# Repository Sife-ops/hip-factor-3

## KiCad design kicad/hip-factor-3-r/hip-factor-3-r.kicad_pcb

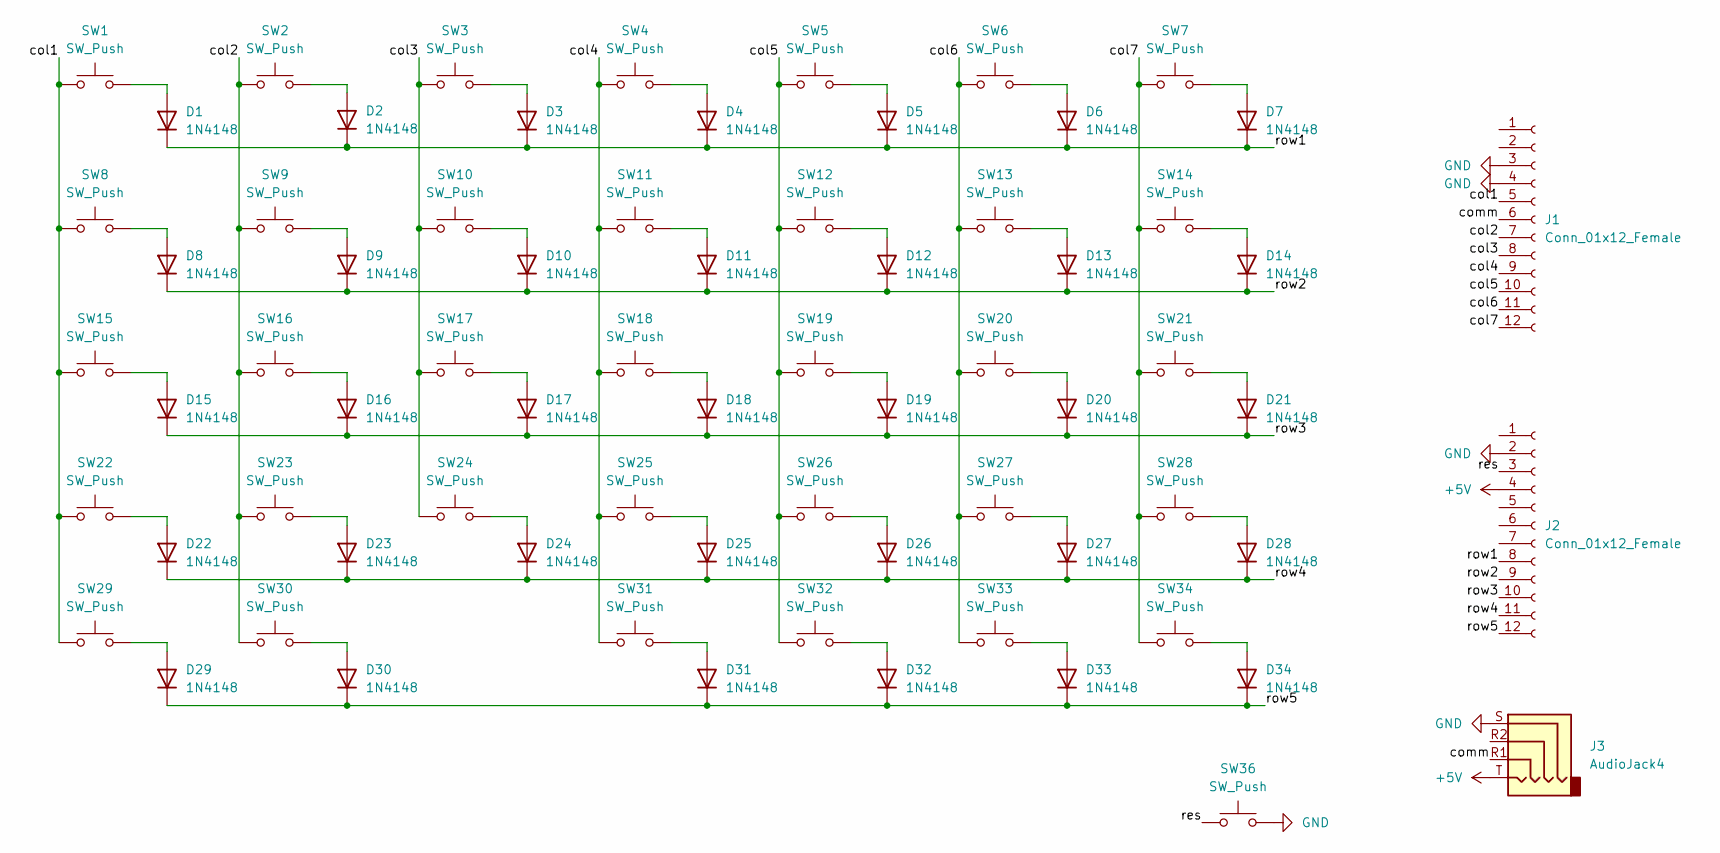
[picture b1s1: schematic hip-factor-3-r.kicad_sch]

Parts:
D1, D2, D3, D4, D5, D6, D7, D8, D9, D10, D11, D12, D13, D14, D15, D16, D17, D18, D19, D20, D21, D22, D23, D24, D25, D26, D27, D28, D29, D30, D31, D32, D33, D34: 1N4148
J1, J2: Conn_01x12_Female; PinHeader_1x12_P2.54mm_Vertical
J3: AudioJack4
SW1, SW2, SW3, SW4, SW5, SW6, SW7, SW8, SW9, SW10, SW11, SW12, SW13, SW14, SW15, SW16, SW17, SW18, SW19, SW20, SW21, SW22, SW23, SW24, SW25, SW26, SW27, SW28, SW29, SW30, SW31, SW32, SW33, SW34: SW_Push; SW_Cherry_MX_1.00u_Plate
SW36: SW_Push

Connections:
+5V: J2.4, J3.T
/col1: J1.5, SW1.1, SW8.1, SW15.1, SW22.1, SW29.1
/col2: J1.7, SW2.1, SW9.1, SW16.1, SW23.1, SW30.1
/col3: J1.8, SW3.1, SW10.1, SW17.1, SW24.1
/col4: J1.9, SW4.1, SW11.1, SW18.1, SW25.1, SW31.1
/col5: J1.10, SW5.1, SW12.1, SW19.1, SW26.1, SW32.1
/col6: J1.11, SW6.1, SW13.1, SW20.1, SW27.1, SW33.1
/col7: J1.12, SW7.1, SW14.1, SW21.1, SW28.1, SW34.1
/comm: J1.6, J3.R1
/res: J2.3, SW36.1
/row1: D1.1 (K), D2.1 (K), D3.1 (K), D4.1 (K), D5.1 (K), D6.1 (K), D7.1 (K), J2.8
/row2: D8.1 (K), D9.1 (K), D10.1 (K), D11.1 (K), D12.1 (K), D13.1 (K), D14.1 (K), J2.9
/row3: D15.1 (K), D16.1 (K), D17.1 (K), D18.1 (K), D19.1 (K), D20.1 (K), D21.1 (K), J2.10
/row4: D22.1 (K), D23.1 (K), D24.1 (K), D25.1 (K), D26.1 (K), D27.1 (K), D28.1 (K), J2.11
/row5: D29.1 (K), D30.1 (K), D31.1 (K), D32.1 (K), D33.1 (K), D34.1 (K), J2.12
GND: J1.3, J1.4, J2.2, J3.S, SW36.2
unnamed: D1.2 (A), SW1.2
unnamed: D2.2 (A), SW2.2
unnamed: D3.2 (A), SW3.2
unnamed: D4.2 (A), SW4.2
unnamed: D5.2 (A), SW5.2
unnamed: D6.2 (A), SW6.2
unnamed: D7.2 (A), SW7.2
unnamed: D8.2 (A), SW8.2
unnamed: D9.2 (A), SW9.2
unnamed: D10.2 (A), SW10.2
unnamed: D11.2 (A), SW11.2
unnamed: D12.2 (A), SW12.2
unnamed: D13.2 (A), SW13.2
unnamed: D14.2 (A), SW14.2
unnamed: D15.2 (A), SW15.2
unnamed: D16.2 (A), SW16.2
unnamed: D17.2 (A), SW17.2
unnamed: D18.2 (A), SW18.2
unnamed: D19.2 (A), SW19.2
unnamed: D20.2 (A), SW20.2
unnamed: D21.2 (A), SW21.2
unnamed: D22.2 (A), SW22.2
unnamed: D23.2 (A), SW23.2
unnamed: D24.2 (A), SW24.2
unnamed: D25.2 (A), SW25.2
unnamed: D26.2 (A), SW26.2
unnamed: D27.2 (A), SW27.2
unnamed: D28.2 (A), SW28.2
unnamed: D29.2 (A), SW29.2
unnamed: D30.2 (A), SW30.2
unnamed: D31.2 (A), SW31.2
unnamed: D32.2 (A), SW32.2
unnamed: D33.2 (A), SW33.2
unnamed: D34.2 (A), SW34.2

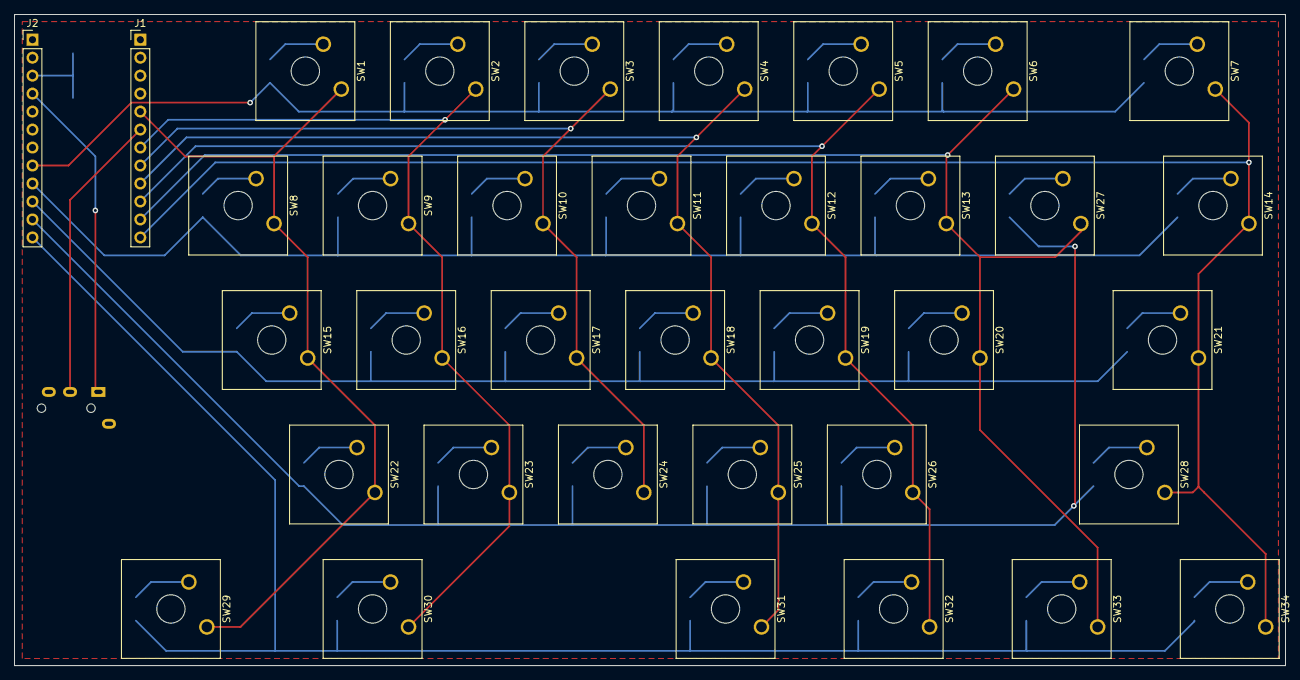
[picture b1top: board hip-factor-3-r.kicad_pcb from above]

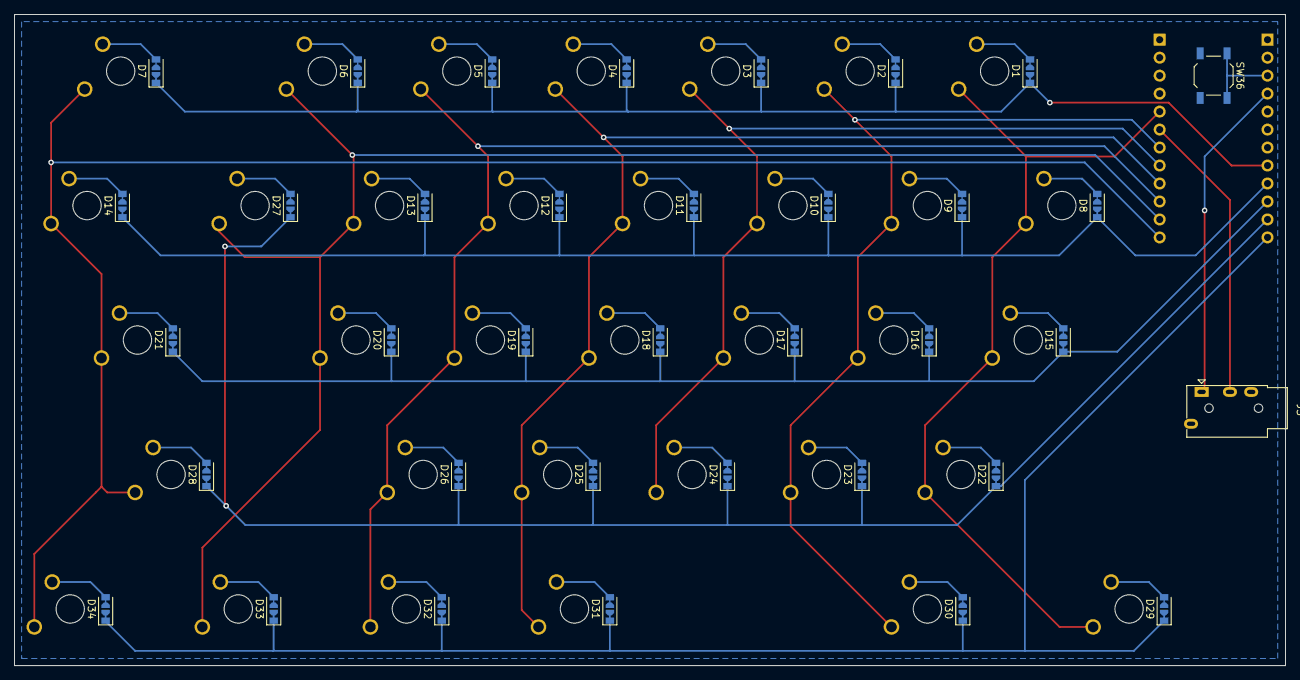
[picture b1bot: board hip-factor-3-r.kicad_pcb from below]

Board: 2 copper layers, 179.6 x 92.0 mm, 72 parts (36 on the bottom side), 50 nets.

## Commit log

2022-03-31 init
2022-04-01 update case model
2022-04-16 update pcb and case
2022-04-16 resize width
2022-04-17 update case
